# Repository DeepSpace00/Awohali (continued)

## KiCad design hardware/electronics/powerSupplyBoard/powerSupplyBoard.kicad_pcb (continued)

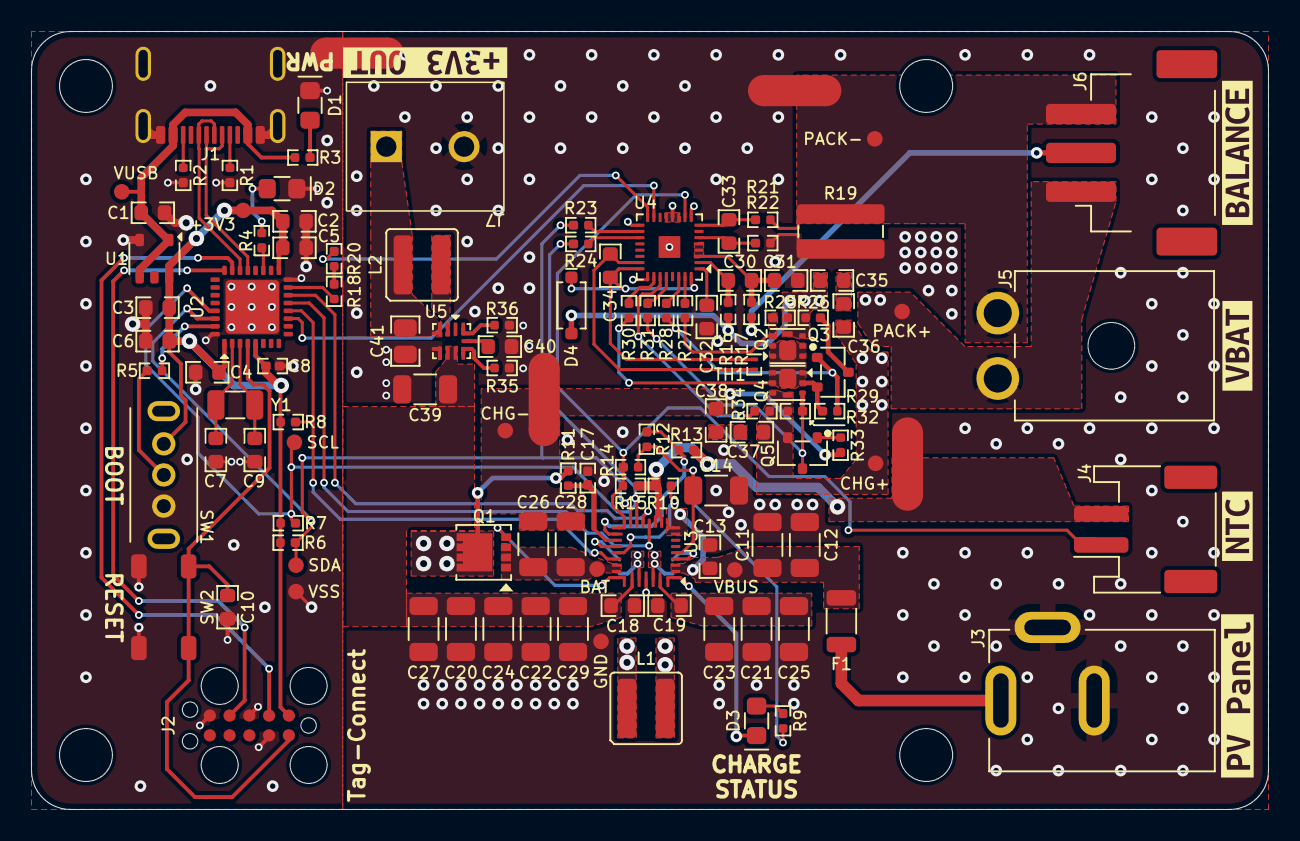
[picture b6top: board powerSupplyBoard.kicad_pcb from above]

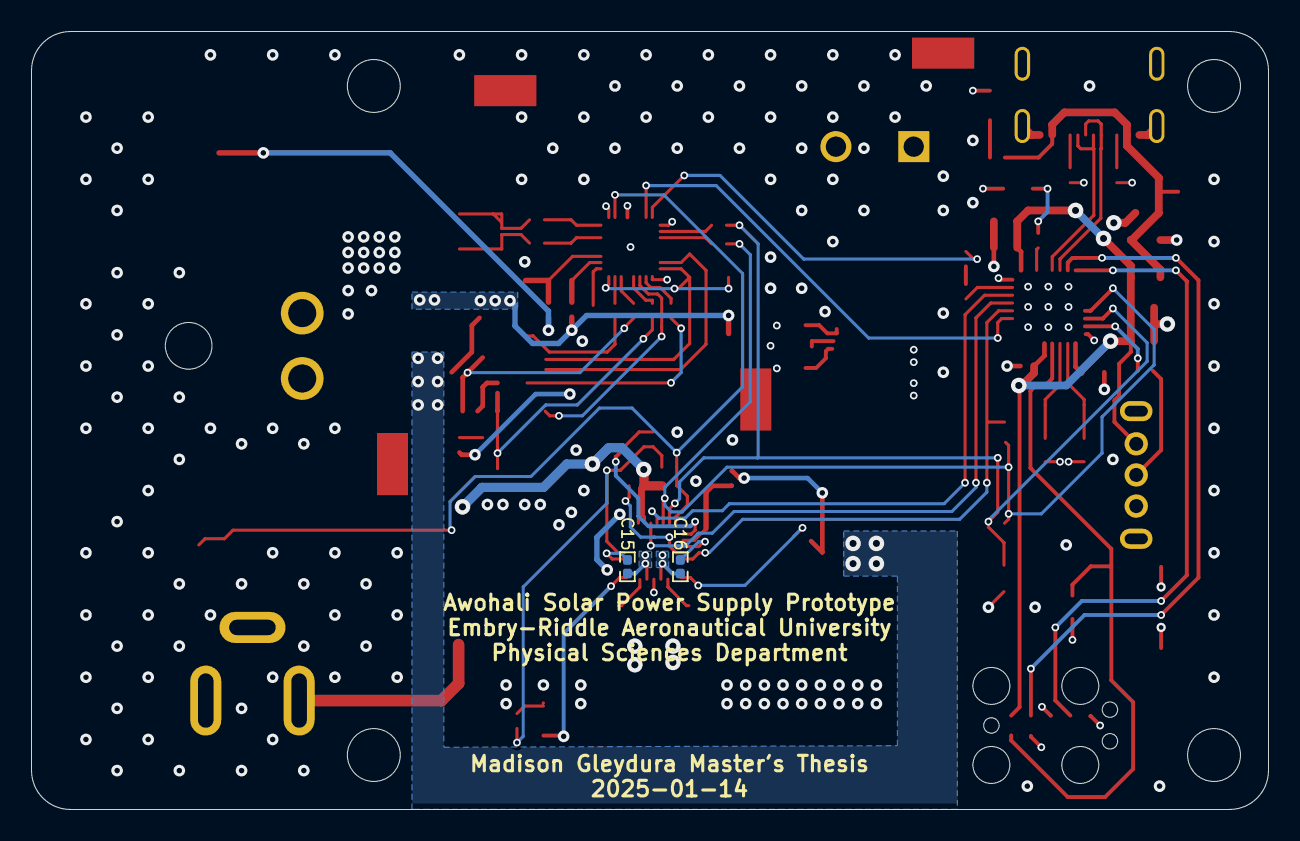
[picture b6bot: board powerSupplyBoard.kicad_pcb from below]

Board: 4 copper layers, 79.5 x 50.0 mm, 130 parts (2 on the bottom side), 77 nets.

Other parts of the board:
kibuzzard-6761C4DA: G***; kibuzzard-6761C4DA
kibuzzard-6761C60F: G***; kibuzzard-6761C60F
kibuzzard-6761CDCC: G***; kibuzzard-6761CDCC
kibuzzard-67280EE7: G***; kibuzzard-67280EE7
kibuzzard-67280F1F: G***; kibuzzard-67280F1F

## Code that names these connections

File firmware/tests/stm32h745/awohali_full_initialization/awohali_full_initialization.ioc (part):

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Mcu.Name=STM32H745ZITx
Mcu.Package=LQFP144
Mcu.UserName=STM32H745ZITx
PA0.GPIOParameters=PinAttribute
PA0.Mode=SD_4_bits_Wide_bus
PA0.PinAttribute=CortexM7
PA0.Signal=SDMMC2_CMD
PA1.GPIOParameters=PinAttribute
PA1.Mode=RMII
PA1.PinAttribute=CortexM7
PA1.Signal=ETH_REF_CLK
PA11.GPIOParameters=PinAttribute
PA11.Mode=Device_Only
PA11.PinAttribute=CortexM7
PA11.Signal=USB_OTG_FS_DM
PA12.GPIOParameters=PinAttribute
PA12.Mode=Device_Only
PA12.PinAttribute=CortexM7
PA12.Signal=USB_OTG_FS_DP
PA13\ (JTMS/SWDIO).GPIOParameters=PinAttribute
PA13\ (JTMS/SWDIO).Mode=Serial_Wire
PA13\ (JTMS/SWDIO).PinAttribute=CortexM7
PA13\ (JTMS/SWDIO).Signal=DEBUG_JTMS-SWDIO
PA14\ (JTCK/SWCLK).GPIOParameters=PinAttribute
PA14\ (JTCK/SWCLK).Mode=Serial_Wire
PA14\ (JTCK/SWCLK).PinAttribute=CortexM7
PA14\ (JTCK/SWCLK).Signal=DEBUG_JTCK-SWCLK
PA2.GPIOParameters=PinAttribute
PA2.Mode=RMII
PA2.PinAttribute=CortexM7
PA2.Signal=ETH_MDIO
PA3.ContextOwner=CortexM4
PA3.GPIOParameters=PinState,GPIO_PuPd,GPIO_Label,PinAttribute
PA3.GPIO_Label=RESET_ETH
PA3.GPIO_PuPd=GPIO_PULLUP
PA3.PinAttribute=CortexM4
PA3.PinState=GPIO_PIN_SET
PA3.Signal=GPIO_Output
PA4.GPIOParameters=PinAttribute
PA4.Mode=NSS_Signal_Hard_Output
PA4.PinAttribute=CortexM4
PA4.Signal=SPI1_NSS
PA5.GPIOParameters=PinAttribute
PA5.Mode=Full_Duplex_Master
PA5.PinAttribute=CortexM4
PA5.Signal=SPI1_SCK
PA6.GPIOParameters=PinAttribute
PA6.Mode=Full_Duplex_Master
PA6.PinAttribute=CortexM4
PA6.Signal=SPI1_MISO
PA7.GPIOParameters=PinAttribute
PA7.Mode=RMII
PA7.PinAttribute=CortexM7
PA7.Signal=ETH_CRS_DV
PA8.GPIOParameters=PinAttribute
PA8.Mode=I2C
PA8.PinAttribute=CortexM4
PA8.Signal=I2C3_SCL
PB0.ContextOwner=CortexM4
PB0.GPIOParameters=GPIO_Label,PinAttribute
PB0.GPIO_Label=HUB_SUSPEND
PB0.PinAttribute=CortexM4
PB0.Signal=GPIO_Output
PB1.ContextOwner=CortexM4
PB1.GPIOParameters=PinState,GPIO_PuPd,GPIO_Label,PinAttribute
PB1.GPIO_Label=RESET_HUB
PB1.GPIO_PuPd=GPIO_PULLUP
PB1.PinAttribute=CortexM4
PB1.PinState=GPIO_PIN_SET
PB1.Signal=GPIO_Output
PB10.GPIOParameters=PinAttribute
PB10.Mode=I2C
PB10.PinAttribute=CortexM4
PB10.Signal=I2C2_SCL
PB11.GPIOParameters=PinAttribute
PB11.Mode=I2C
PB11.PinAttribute=CortexM4
PB11.Signal=I2C2_SDA
PB12.GPIOParameters=PinAttribute
PB12.Mode=RMII
PB12.PinAttribute=CortexM7
PB12.Signal=ETH_TXD0
PB13.GPIOParameters=PinAttribute
PB13.Mode=RMII
PB13.PinAttribute=CortexM7
PB13.Signal=ETH_TXD1
PB14.GPIOParameters=PinAttribute
PB14.Mode=SD_4_bits_Wide_bus
PB14.PinAttribute=CortexM7
PB14.Signal=SDMMC2_D0
PB15.GPIOParameters=PinAttribute
PB15.Mode=SD_4_bits_Wide_bus
PB15.PinAttribute=CortexM7
PB15.Signal=SDMMC2_D1
PB2.ContextOwner=CortexM7
PB2.GPIOParameters=GPIO_Label,PinAttribute
PB2.GPIO_Label=HUB_H7_INT
PB2.PinAttribute=CortexM7
PB2.Signal=GPXTI2
PB3\ (JTDO/TRACESWO).GPIOParameters=PinAttribute
PB3\ (JTDO/TRACESWO).Mode=SD_4_bits_Wide_bus
PB3\ (JTDO/TRACESWO).PinAttribute=CortexM7
PB3\ (JTDO/TRACESWO).Signal=SDMMC2_D2
PB4\ (NJTRST).GPIOParameters=PinAttribute
PB4\ (NJTRST).Mode=SD_4_bits_Wide_bus
PB4\ (NJTRST).PinAttribute=CortexM7
PB4\ (NJTRST).Signal=SDMMC2_D3
PB6.GPIOParameters=PinAttribute
PB6.Mode=I2C
PB6.PinAttribute=CortexM4
PB6.Signal=I2C1_SCL
PB7.GPIOParameters=PinAttribute
PB7.Mode=I2C
PB7.PinAttribute=CortexM4
PB7.Signal=I2C1_SDA
PB9.ContextOwner=CortexM4
PB9.GPIOParameters=GPIO_Label,PinAttribute
PB9.GPIO_Label=NEOPIXEL
PB9.PinAttribute=CortexM4
PB9.Signal=GPIO_Output
PC1.GPIOParameters=PinAttribute
PC1.Mode=RMII
PC1.PinAttribute=CortexM7
PC1.Signal=ETH_MDC
PC10.GPIOParameters=PinAttribute
PC10.Mode=Asynchronous
PC10.PinAttribute=CortexM7
PC10.Signal=UART4_TX
PC11.GPIOParameters=PinAttribute
PC11.Mode=Asynchronous
PC11.PinAttribute=CortexM7
PC11.Signal=UART4_RX
PC13.ContextOwner=CortexM4
PC13.GPIOParameters=GPIO_PuPd,GPIO_Label,PinAttribute
PC13.GPIO_Label=LTE_PWR_EN
PC13.GPIO_PuPd=GPIO_NOPULL
PC13.PinAttribute=CortexM4
PC13.Signal=GPIO_Output
PC14-OSC32_IN\ (OSC32_IN).GPIOParameters=PinAttribute
PC14-OSC32_IN\ (OSC32_IN).Mode=LSE-External-Clock-Source
PC14-OSC32_IN\ (OSC32_IN).PinAttribute=Free
PC14-OSC32_IN\ (OSC32_IN).Signal=RCC_OSC32_IN
PC15-OSC32_OUT\ (OSC32_OUT).ContextOwner=CortexM4
PC15-OSC32_OUT\ (OSC32_OUT).GPIOParameters=PinAttribute
PC15-OSC32_OUT\ (OSC32_OUT).PinAttribute=CortexM4
PC15-OSC32_OUT\ (OSC32_OUT).Signal=GPIO_Output
PC2_C.ContextOwner=CortexM4
PC2_C.GPIOParameters=GPIO_Label,PinAttribute
PC2_C.GPIO_Label=SPI_GRANT
PC2_C.PinAttribute=CortexM4
PC2_C.Signal=GPIO_Output
PC3_C.ContextOwner=CortexM4
PC3_C.GPIOParameters=GPIO_Label,PinAttribute
PC3_C.GPIO_Label=SPI_REQ
PC3_C.PinAttribute=CortexM4
PC3_C.Signal=GPIO_Output
PC4.GPIOParameters=PinAttribute
PC4.Mode=RMII
PC4.PinAttribute=CortexM7
PC4.Signal=ETH_RXD0
PC5.GPIOParameters=PinAttribute
PC5.Mode=RMII
PC5.PinAttribute=CortexM7
PC5.Signal=ETH_RXD1
PC9.GPIOParameters=PinAttribute
PC9.Mode=I2C
PC9.PinAttribute=CortexM4
PC9.Signal=I2C3_SDA
PD0.GPIOParameters=PinAttribute
PD0.Mode=FDCAN_Activate
PD0.PinAttribute=CortexM4
PD0.Signal=FDCAN1_RX
PD1.GPIOParameters=PinAttribute
PD1.Mode=FDCAN_Activate
PD1.PinAttribute=CortexM4
PD1.Signal=FDCAN1_TX
PD2.ContextOwner=CortexM4
PD2.GPIOParameters=GPIO_Label,PinAttribute
PD2.GPIO_Label=H7_CAN_STB
PD2.PinAttribute=CortexM4
PD2.Signal=GPIO_Output
PD3.ContextOwner=CortexM4
PD3.GPIOParameters=GPIO_Label,PinAttribute
PD3.GPIO_Label=RESET_L4_H7
PD3.PinAttribute=CortexM4
PD3.Signal=GPIO_Output
PD4.ContextOwner=CortexM4
PD4.GPIOParameters=GPIO_Label,PinAttribute
PD4.GPIO_Label=BOOT0_L4
PD4.PinAttribute=CortexM4
PD4.Signal=GPIO_Output
PD5.ContextOwner=CortexM4
PD5.GPIOParameters=GPIO_Label,PinAttribute
PD5.GPIO_Label=SPI_SS_L4
PD5.PinAttribute=CortexM4
PD5.Signal=GPXTI5
PD6.GPIOParameters=PinAttribute
PD6.Mode=SD_4_bits_Wide_bus
PD6.PinAttribute=CortexM7
PD6.Signal=SDMMC2_CK
PD7.GPIOParameters=PinAttribute
PD7.Mode=Full_Duplex_Master
PD7.PinAttribute=CortexM4
PD7.Signal=SPI1_MOSI
PD8.GPIOParameters=PinAttribute
PD8.Mode=Asynchronous
PD8.PinAttribute=CortexM4
PD8.Signal=USART3_TX
PD9.GPIOParameters=PinAttribute
PD9.Mode=Asynchronous
PD9.PinAttribute=CortexM4
PD9.Signal=USART3_RX
PE10.ContextOwner=CortexM4
PE10.GPIOParameters=GPIO_Label,PinAttribute
PE10.GPIO_Label=GNSS_PWR_EN
PE10.PinAttribute=CortexM4
PE10.Signal=GPIO_Output
PE11.ContextOwner=CortexM7
PE11.GPIOParameters=GPIO_Label,PinAttribute
PE11.GPIO_Label=GNSS_TX_RDY
PE11.PinAttribute=CortexM7
PE11.Signal=GPIO_Input
PE12.ContextOwner=CortexM7
PE12.GPIOParameters=GPIO_Label,PinAttribute
PE12.GPIO_Label=GNSS_INT
PE12.PinAttribute=CortexM7
PE12.Signal=GPXTI12
PE13.ContextOwner=CortexM7
PE13.GPIOParameters=GPIO_Label,PinAttribute
PE13.GPIO_Label=GNSS_PPS
PE13.PinAttribute=CortexM7
PE13.Signal=GPIO_Input
PE14.ContextOwner=CortexM4
PE14.GPIOParameters=PinState,GPIO_PuPd,GPIO_Label,PinAttribute
PE14.GPIO_Label=RESET_GNSS
PE14.GPIO_PuPd=GPIO_PULLUP
PE14.PinAttribute=CortexM4
PE14.PinState=GPIO_PIN_SET
PE14.Signal=GPIO_Output
PE2.GPIOParameters=PinAttribute
PE2.Mode=Single Bank 1
PE2.PinAttribute=CortexM7
PE2.Signal=QUADSPI_BK1_IO2
PE3.ContextOwner=CortexM4
PE3.GPIOParameters=PinState,GPIO_Label,PinAttribute
PE3.GPIO_Label=RESET_LTE
PE3.PinAttribute=CortexM4
PE3.PinState=GPIO_PIN_SET
PE3.Signal=GPIO_Output
PE4.ContextOwner=CortexM7
PE4.GPIOParameters=GPIO_Label,PinAttribute
PE4.GPIO_Label=MOD_STS
PE4.PinAttribute=CortexM7
PE4.Signal=GPIO_Input
PE5.ContextOwner=CortexM7
PE5.GPIOParameters=GPIO_Label,PinAttribute
PE5.GPIO_Label=NET_STS
PE5.PinAttribute=CortexM7
PE5.Signal=GPIO_Input
PE6.ContextOwner=CortexM4
PE6.GPIOParameters=GPIO_Label,PinAttribute
PE6.GPIO_Label=LTE_SLEEP
PE6.PinAttribute=CortexM4
PE6.Signal=GPIO_Output
PF10.GPIOParameters=PinAttribute
PF10.Mode=Single Bank 1
PF10.PinAttribute=CortexM7
PF10.Signal=QUADSPI_CLK
PF6.GPIOParameters=PinAttribute
PF6.Mode=Single Bank 1
PF6.PinAttribute=CortexM7
PF6.Signal=QUADSPI_BK1_IO3
PF8.GPIOParameters=PinAttribute
PF8.Mode=Single Bank 1
PF8.PinAttribute=CortexM7
PF8.Signal=QUADSPI_BK1_IO0
PF9.GPIOParameters=PinAttribute
PF9.Mode=Single Bank 1
PF9.PinAttribute=CortexM7
PF9.Signal=QUADSPI_BK1_IO1
PG11.GPIOParameters=PinAttribute
PG11.Mode=RMII
PG11.PinAttribute=CortexM7
PG11.Signal=ETH_TX_EN
PG6.GPIOParameters=PinAttribute
PG6.Mode=Single Bank 1
PG6.PinAttribute=CortexM7
PG6.Signal=QUADSPI_BK1_NCS
PH0-OSC_IN\ (PH0).GPIOParameters=PinAttribute
PH0-OSC_IN\ (PH0).Mode=HSE-External-Clock-Source
PH0-OSC_IN\ (PH0).PinAttribute=Free
PH0-OSC_IN\ (PH0).Signal=RCC_OSC_IN
RCC.SYSCLKFreq_VALUE=64000000
board=custom

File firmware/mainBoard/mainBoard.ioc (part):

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Mcu.Name=STM32H745ZITx
Mcu.Package=LQFP144
Mcu.UserName=STM32H745ZITx
PA0.GPIOParameters=PinAttribute
PA0.Mode=SD_4_bits_Wide_bus
PA0.PinAttribute=CortexM7
PA0.Signal=SDMMC2_CMD
PA1.GPIOParameters=PinAttribute
PA1.Mode=RMII
PA1.PinAttribute=CortexM7
PA1.Signal=ETH_REF_CLK
PA11.GPIOParameters=PinAttribute
PA11.Mode=Device_Only
PA11.PinAttribute=CortexM7
PA11.Signal=USB_OTG_FS_DM
PA12.GPIOParameters=PinAttribute
PA12.Mode=Device_Only
PA12.PinAttribute=CortexM7
PA12.Signal=USB_OTG_FS_DP
PA13\ (JTMS/SWDIO).GPIOParameters=PinAttribute
PA13\ (JTMS/SWDIO).Mode=Serial_Wire
PA13\ (JTMS/SWDIO).PinAttribute=CortexM7
PA13\ (JTMS/SWDIO).Signal=DEBUG_JTMS-SWDIO
PA14\ (JTCK/SWCLK).GPIOParameters=PinAttribute
PA14\ (JTCK/SWCLK).Mode=Serial_Wire
PA14\ (JTCK/SWCLK).PinAttribute=CortexM7
PA14\ (JTCK/SWCLK).Signal=DEBUG_JTCK-SWCLK
PA2.GPIOParameters=PinAttribute
PA2.Mode=RMII
PA2.PinAttribute=CortexM7
PA2.Signal=ETH_MDIO
PA7.GPIOParameters=PinAttribute
PA7.Mode=RMII
PA7.PinAttribute=CortexM7
PA7.Signal=ETH_CRS_DV
PA8.GPIOParameters=PinAttribute
PA8.Mode=I2C
PA8.PinAttribute=CortexM7
PA8.Signal=I2C3_SCL
PB10.GPIOParameters=PinAttribute
PB10.Mode=I2C
PB10.PinAttribute=CortexM7
PB10.Signal=I2C2_SCL
PB11.GPIOParameters=PinAttribute
PB11.Mode=I2C
PB11.PinAttribute=CortexM7
PB11.Signal=I2C2_SDA
PB12.GPIOParameters=PinAttribute
PB12.Mode=RMII
PB12.PinAttribute=CortexM7
PB12.Signal=ETH_TXD0
PB13.GPIOParameters=PinAttribute
PB13.Mode=RMII
PB13.PinAttribute=CortexM7
PB13.Signal=ETH_TXD1
PB14.GPIOParameters=PinAttribute
PB14.Mode=SD_4_bits_Wide_bus
PB14.PinAttribute=CortexM7
PB14.Signal=SDMMC2_D0
PB15.GPIOParameters=PinAttribute
PB15.Mode=SD_4_bits_Wide_bus
PB15.PinAttribute=CortexM7
PB15.Signal=SDMMC2_D1
PB3\ (JTDO/TRACESWO).GPIOParameters=PinAttribute
PB3\ (JTDO/TRACESWO).Mode=SD_4_bits_Wide_bus
PB3\ (JTDO/TRACESWO).PinAttribute=CortexM7
PB3\ (JTDO/TRACESWO).Signal=SDMMC2_D2
PB4\ (NJTRST).GPIOParameters=PinAttribute
PB4\ (NJTRST).Mode=SD_4_bits_Wide_bus
PB4\ (NJTRST).PinAttribute=CortexM7
PB4\ (NJTRST).Signal=SDMMC2_D3
PB6.GPIOParameters=PinAttribute
PB6.Mode=I2C
PB6.PinAttribute=CortexM7
PB6.Signal=I2C1_SCL
PB7.GPIOParameters=PinAttribute
PB7.Mode=I2C
PB7.PinAttribute=CortexM7
PB7.Signal=I2C1_SDA
PC1.GPIOParameters=PinAttribute
PC1.Mode=RMII
PC1.PinAttribute=CortexM7
PC1.Signal=ETH_MDC
PC10.GPIOParameters=PinAttribute
PC10.Mode=Asynchronous
PC10.PinAttribute=CortexM7
PC10.Signal=UART4_TX
PC11.GPIOParameters=PinAttribute
PC11.Mode=Asynchronous
PC11.PinAttribute=CortexM7
PC11.Signal=UART4_RX
PC12.GPIOParameters=PinAttribute
PC12.Mode=Asynchronous
PC12.PinAttribute=CortexM7
PC12.Signal=UART5_TX
PC14-OSC32_IN\ (OSC32_IN).GPIOParameters=PinAttribute
PC14-OSC32_IN\ (OSC32_IN).Mode=LSE-External-Clock-Source
PC14-OSC32_IN\ (OSC32_IN).PinAttribute=Free
PC14-OSC32_IN\ (OSC32_IN).Signal=RCC_OSC32_IN
PC4.GPIOParameters=PinAttribute
PC4.Mode=RMII
PC4.PinAttribute=CortexM7
PC4.Signal=ETH_RXD0
PC5.GPIOParameters=PinAttribute
PC5.Mode=RMII
PC5.PinAttribute=CortexM7
PC5.Signal=ETH_RXD1
PC7.GPIOParameters=PinAttribute
PC7.Mode=Asynchronous
PC7.PinAttribute=CortexM7
PC7.Signal=USART6_RX
PC9.GPIOParameters=PinAttribute
PC9.Mode=I2C
PC9.PinAttribute=CortexM7
PC9.Signal=I2C3_SDA
PD0.GPIOParameters=PinAttribute
PD0.Mode=FDCAN_Activate
PD0.PinAttribute=CortexM7
PD0.Signal=FDCAN1_RX
PD1.GPIOParameters=PinAttribute
PD1.Mode=FDCAN_Activate
PD1.PinAttribute=CortexM7
PD1.Signal=FDCAN1_TX
PD11.GPIOParameters=PinAttribute
PD11.Mode=CTS_RTS
PD11.PinAttribute=CortexM7
PD11.Signal=USART3_CTS
PD12.GPIOParameters=PinAttribute
PD12.Mode=CTS_RTS
PD12.PinAttribute=CortexM7
PD12.Signal=USART3_RTS
PD2.GPIOParameters=PinAttribute
PD2.Mode=Asynchronous
PD2.PinAttribute=CortexM7
PD2.Signal=UART5_RX
PD6.GPIOParameters=PinAttribute
PD6.Mode=SD_4_bits_Wide_bus
PD6.PinAttribute=CortexM7
PD6.Signal=SDMMC2_CK
PD8.GPIOParameters=PinAttribute
PD8.Mode=Asynchronous
PD8.PinAttribute=CortexM7
PD8.Signal=USART3_TX
PD9.GPIOParameters=PinAttribute
PD9.Mode=Asynchronous
PD9.PinAttribute=CortexM7
PD9.Signal=USART3_RX
PE2.GPIOParameters=PinAttribute
PE2.Mode=Single Bank 1
PE2.PinAttribute=CortexM7
PE2.Signal=QUADSPI_BK1_IO2
PE7.GPIOParameters=PinAttribute
PE7.Mode=Asynchronous
PE7.PinAttribute=CortexM7
PE7.Signal=UART7_RX
PF10.GPIOParameters=PinAttribute
PF10.Mode=Single Bank 1
PF10.PinAttribute=CortexM7
PF10.Signal=QUADSPI_CLK
PF14.GPIOParameters=PinAttribute
PF14.Mode=I2C
PF14.PinAttribute=CortexM7
PF14.Signal=I2C4_SCL
PF15.GPIOParameters=PinAttribute
PF15.Mode=I2C
PF15.PinAttribute=CortexM7
PF15.Signal=I2C4_SDA
PF6.GPIOParameters=PinAttribute
PF6.Mode=Single Bank 1
PF6.PinAttribute=CortexM7
PF6.Signal=QUADSPI_BK1_IO3
PF7.GPIOParameters=PinAttribute
PF7.Mode=Asynchronous
PF7.PinAttribute=CortexM7
PF7.Signal=UART7_TX
PF8.GPIOParameters=PinAttribute
PF8.Mode=Single Bank 1
PF8.PinAttribute=CortexM7
PF8.Signal=QUADSPI_BK1_IO0
PF9.GPIOParameters=PinAttribute
PF9.Mode=Single Bank 1
PF9.PinAttribute=CortexM7
PF9.Signal=QUADSPI_BK1_IO1
PG11.GPIOParameters=PinAttribute
PG11.Mode=RMII
PG11.PinAttribute=CortexM7
PG11.Signal=ETH_TX_EN
PG13.GPIOParameters=PinAttribute
PG13.Mode=CTS_RTS
PG13.PinAttribute=CortexM7
PG13.Signal=USART6_CTS
PG14.GPIOParameters=PinAttribute
PG14.Mode=Asynchronous
PG14.PinAttribute=CortexM7
PG14.Signal=USART6_TX
PG6.GPIOParameters=PinAttribute
PG6.Mode=Single Bank 1
PG6.PinAttribute=CortexM7
PG6.Signal=QUADSPI_BK1_NCS
PG8.GPIOParameters=PinAttribute
PG8.Mode=CTS_RTS
PG8.PinAttribute=CortexM7
PG8.Signal=USART6_RTS
PH0-OSC_IN\ (PH0).GPIOParameters=PinAttribute
PH0-OSC_IN\ (PH0).Mode=HSE-External-Clock-Source
PH0-OSC_IN\ (PH0).PinAttribute=Free
PH0-OSC_IN\ (PH0).Signal=RCC_OSC_IN
RCC.SYSCLKFreq_VALUE=64000000
board=custom

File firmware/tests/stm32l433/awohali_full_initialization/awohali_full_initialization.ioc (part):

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Mcu.Name=STM32L433C(B-C)Ux
Mcu.Package=UFQFPN48
Mcu.UserName=STM32L433CCUx
PA0.GPIOParameters=GPIO_Label
PA0.GPIO_Label=CAN_STB
PA0.Signal=GPIO_Output
PA1.Mode=Full_Duplex_Master
PA1.Signal=SPI1_SCK
PA10.Mode=I2C
PA10.Signal=I2C1_SDA
PA11.Mode=Device
PA11.Signal=USB_DM
PA12.Mode=Device
PA12.Signal=USB_DP
PA13\ (JTMS-SWDIO).Mode=Serial_Wire
PA13\ (JTMS-SWDIO).Signal=SYS_JTMS-SWDIO
PA14\ (JTCK-SWCLK).Mode=Serial_Wire
PA14\ (JTCK-SWCLK).Signal=SYS_JTCK-SWCLK
PA15\ (JTDI).GPIOParameters=GPIO_Label
PA15\ (JTDI).GPIO_Label=PG_2V8
PA15\ (JTDI).Signal=GPIO_Input
PA2.GPIOParameters=GPIO_Label
PA2.GPIO_Label=BAT_CHG_INT
PA2.Signal=GPXTI2
PA3.GPIOParameters=PinState,GPIO_Label
PA3.GPIO_Label=EEPROM_WC
PA3.PinState=GPIO_PIN_SET
PA3.Signal=GPIO_Output
PA4.Mode=NSS_Signal_Hard_Output
PA4.Signal=SPI1_NSS
PA5.GPIOParameters=GPIO_Label
PA5.GPIO_Label=BOOT_H7
PA5.Signal=GPIO_Output
PA6.Mode=Full_Duplex_Master
PA6.Signal=SPI1_MISO
PA7.Mode=Full_Duplex_Master
PA7.Signal=SPI1_MOSI
PA8.GPIOParameters=GPIO_Label
PA8.GPIO_Label=SS_L4
PA8.Signal=GPIO_Input
PA9.Mode=I2C
PA9.Signal=I2C1_SCL
PB1.GPIOParameters=GPIO_Label
PB1.GPIO_Label=PG_1V8
PB1.Signal=GPIO_Input
PB10.GPIOParameters=GPIO_Label
PB10.GPIO_Label=PG_3V3
PB10.Signal=GPIO_Input
PB11.GPIOParameters=GPIO_Label
PB11.GPIO_Label=BAL_ALERT
PB11.Signal=GPIO_Input
PB12.GPIOParameters=GPIO_Label
PB12.GPIO_Label=SPI1_GRANT
PB12.Signal=GPIO_Output
PB13.GPIOParameters=GPIO_Label
PB13.GPIO_Label=SPI1_REQ
PB13.Signal=GPIO_Output
PB14.GPIOParameters=PinState,GPIO_Label
PB14.GPIO_Label=QON
PB14.PinState=GPIO_PIN_SET
PB14.Signal=GPIO_Output
PB15.GPIOParameters=PinState,GPIO_Label
PB15.GPIO_Label=CE
PB15.PinState=GPIO_PIN_SET
PB15.Signal=GPIO_Output
PB2.GPIOParameters=GPIO_Label
PB2.GPIO_Label=EN_1V8
PB2.Signal=GPIO_Output
PB3\ (JTDO-TRACESWO).GPIOParameters=GPIO_Label
PB3\ (JTDO-TRACESWO).GPIO_Label=EN_2V8
PB3\ (JTDO-TRACESWO).Signal=GPIO_Output
PB4\ (NJTRST).GPIOParameters=GPIO_Label
PB4\ (NJTRST).GPIO_Label=RESET_H7
PB4\ (NJTRST).Signal=GPIO_Output
PB6.GPIOParameters=GPIO_Label
PB6.GPIO_Label=HUB_INT
PB6.Signal=GPXTI6
PB8.Mode=CAN_Activate
PB8.Signal=CAN1_RX
PB9.Mode=CAN_Activate
PB9.Signal=CAN1_TX
PC14-OSC32_IN\ (PC14).Mode=LSE-External-Clock-Source
PC14-OSC32_IN\ (PC14).Signal=RCC_OSC32_IN
PH0-OSC_IN\ (PH0).GPIOParameters=GPIO_Label
PH0-OSC_IN\ (PH0).GPIO_Label=NEOPIXEL_DIN
PH0-OSC_IN\ (PH0).Signal=GPIO_Output
PH1-OSC_OUT\ (PH1).GPIOParameters=GPIO_Label
PH1-OSC_OUT\ (PH1).GPIO_Label=LED_BUILTIN
PH1-OSC_OUT\ (PH1).Signal=GPIO_Output
RCC.HSE_VALUE=8000000
RCC.SYSCLKFreq_VALUE=80000000
RCC.SYSCLKSource=RCC_SYSCLKSOURCE_PLLCLK
board=custom

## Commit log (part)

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2025-08-18 removed unneeded wire instance
2025-08-18 removed unneeded serial instance
2025-08-18 dont need to init serial here
2025-08-18 dont need to set init flag here
2025-08-18 redundant
2025-08-18 init i2c stuff
2025-08-18 don't need deinit function
2025-08-18 init uart stuff
2025-08-18 set status type
2025-08-18 made address const
2025-08-18 removed unneeded vars
2025-08-18 gnss driver stuff
2025-08-19 rewrote GNSS driver
2025-08-22 added functions to get ubx-mon-ver info
2025-08-22 redid example to just get version info
    Just a test to make sure we can establish communication with the module
2025-08-25 created examples for gnss
2025-08-27 renamed folders
2025-09-10 added tests for setting up GNSS LNA for testing
2025-09-10 set up GNSS LNA testing
2025-09-10 updated driver to better handle UBX commands. added layer param to config functions.
2025-09-10 fixed typedefs and rearanged stuff
2025-09-11 fixed driver
2025-09-11 added words to dict
2025-09-11 added pyubx2 package req
2025-09-11 moved file
2025-09-11 testing parsing UBX data file
2025-09-11 switched data message type
2025-09-14 fixed driver i think. added script to record data
2025-09-15 changes ig
2025-09-18 created files
2025-09-18 finally got GPS logging working
2025-09-18 new data files
2025-09-18 fixed timing and disabled galileo and glonass
2025-09-18 new data
2025-09-19 new data!
2025-09-19 fixed parser to properly timestamp data
2025-09-19 debug statements
2025-09-19 path stuff from saving
2025-09-19 moved data
2025-09-19 added pandas to deps
2025-09-19 time stuff
2025-09-19 converted file for UBX 2
2025-09-19 cleaned up code
2025-09-19 new (good) data!
2025-09-19 paths
2025-09-19 added Galileo sats and reverted message rate back to 1Hz
2025-09-23 more data
2025-09-23 measurement rate
2025-09-23 whatever this xml stuff is ig
2025-09-23 setup gnss logging stm32 projects for both cores
2025-09-26 started writing new logging code
2025-09-28 data
2025-09-28 trying to fix RAWX nav rate
2025-09-28 finally, some good data
2025-09-28 we need a .gitignore for this stuff
2025-09-28 command for parsing ubx file
2025-09-28 git ignore for CLion XML files. finally...
2025-09-28 removed old XML files
2025-09-29 python stuff
2025-09-29 created new ubx parser for more message types
2025-09-29 fixed for logging more messages
2025-09-29 fixed nav rate
2025-09-29 removed pyubx2 package. manually parsing ubx files now
2025-09-29 added root build dir
2025-09-29 editor changes
2025-09-29 fix addresses
2025-09-29 processing data
2025-09-29 copied latest driver to src folder
2025-09-29 deleted blank line
2025-10-01 adding USB hub initialization to program
2025-10-01 removed uneeded build, cache, and editor files
2025-10-02 evk data
2025-10-02 data!
2025-10-03 unneeded scripts
2025-10-03 old files
2025-10-03 new JSONs
2025-10-03 fixed scripts
2025-10-03 test data
2025-10-03 renamed files
2025-10-03 processed new data
2025-10-05 fixing code to log on mainboard
2025-10-07 data logged with pygpsclient
2025-10-08 files deleted
2025-10-08 added CLion ignores
2025-10-08 c_cpp_properties for workspace
2025-10-08 not sure. going to stop tracking anyways
2025-10-08 test to init usb hub with STM32H745
2025-10-08 moved to new temp dir until other system stuff is fixed
2025-10-08 removed untracked files
2025-10-08 removed files
2025-10-08 re-added submodule
2025-10-13 removed some files from .gitignore
2025-10-13 readded files
2025-10-13 removed .iml ignore
2025-10-13 iml's
2025-10-13 clean blink example for CubeIDE
2025-10-13 broken
2025-10-13 playing with settings
2025-10-13 trying to get it working
2025-10-13 clean CLion CMake example. use this as a template for new projects. does work (on office PC, need to test for home)
2025-10-13 renamed folder
2025-10-13 generated files
2025-10-13 configured for build
2025-10-15 removed
2025-10-15 modified for USB hub init only
2025-10-15 added USB hub files
2025-10-15 removed FatFs files
2025-10-15 fixed blink code location
2025-10-15 added USB stuff to main.h
2025-10-15 removed unneeded HALs
2025-10-15 added usb init code
2025-10-15 removed old GPIO clock stuff
2025-10-15 added usb hub stuff
2025-11-10 radar beam blockage - KGSP
2025-11-13 exported cad
2025-11-13 workspace stuff
2025-11-13 fixing ephemeric and georange code
2025-11-13 remove image
2025-11-14 created new sfrbx parser to make sure it is 100% correct.
2025-11-14 replaced with new file
2025-11-14 new ephemeris data
2025-11-14 table structure for message types
2025-11-14 pycharm stuff
2025-11-14 moved to subfolder
2025-11-14 moved to data folder
2025-11-14 moved to "old" subfolder
2025-11-17 trying to get Galileo code working
2025-11-17 working Galileo ephemeris parser
2025-11-18 working ephemeris for Galileo
2025-11-18 fixing geometric range code
2025-11-18 exported model for LPS28 mount
2025-11-21 removed old files
2025-11-21 RINEX data from Ormond BEach municipal airport CORS receiver
2025-11-21 parsed ephemeris data from CORS
2025-11-21 old versions
2025-11-21 renamed file
2025-11-21 fixed code with correct time corrections
2025-11-21 examples for how to call functions from geometric_range
2025-11-21 some pycharm file. might need to add to gitignore
2025-11-21 fixed mount profiles
2025-11-21 UBX data from 2025-10-03
2025-11-24 Working on fixing timing issues
2025-11-24 moved ephemerides to subfolder
2025-11-24 renamed files and moved to old folder
2025-11-24 broke out into separate file
2025-11-24 fixed code
2025-11-24 reformatted name for sqrt_A parameter
2025-11-24 contains all stuff including clock correction
2025-11-24 limited to only calculating geometric range
2025-11-24 calculating pseudorange residuals (primarily tropospheric delay)
2025-11-25 CLion stuff
2025-11-25 fixed printf type formatting and temporarily disabled coordinate logging
2025-11-25 calc for new data
2025-11-25 removed CSVs
2025-11-26 moved files
2025-11-26 without utc timestamp
2025-11-26 modified code
2025-11-26 code to analyze pseudorange
2025-11-26 unsorted data
2025-11-30 fixes to code to process all data
2025-11-30 ormond beach data
2025-11-30 ESA data
2025-11-30 plots
2025-11-30 sample data
2025-11-30 parsed ubx data
2025-11-30 database files
2025-11-30 todo list
2025-11-30 rinex broadcast ephemeris
2025-11-30 fixing code
2025-11-30 new ephemeris
2025-12-01 added clarification for what ephemeris is considered valid
2025-12-01 fixed dict structures
2025-12-01 cleaned up vars, set ref time to gpsTOW, and new data dirs
2025-12-01 fixed some stuff related to gpsTOW and getting ZED-F9P data to look right
2025-12-01 trying to see what is going on with ZED-F9P data
2025-12-01 updated .gitignore
2025-12-01 stop tracking PyCharm workspace file
2025-12-01 Stop traching PyCharm cpython files
2025-12-01 re-ran data
2025-12-01 fixed rcv bias calc
2025-12-01 stop tracking
2025-12-01 added pycache to gitignore
2025-12-03 best data so far
2025-12-03 csv output from db
2025-12-03 added code to fix iTOW/rcvTOW syncing issues
2025-12-08 created
2025-12-09 pwv data
2025-12-09 VMF stuff
2025-12-10 fixed code for ZTD and added ionosphere correction stuff
2025-12-20 simplified code and added more message types in driver
2025-12-20 removed old example
2025-12-20 updated driver
2025-12-20 changed plots
2025-12-27 trying to port datalogger code to Pico-SDK
2025-12-27 stoped tracking files
2025-12-27 ignore .idea/ dir
2025-12-27 Pico SDK version of gnss datalogger
2025-12-27 added UART DMA control
2025-12-27 globally ignore any .idea/ directory
2025-12-27 stop tracking files
2025-12-27 stopped tracking files
2025-12-27 renamed dirs
2025-12-27 moved images
2025-12-27 updated datasheet refs
2025-12-27 re-plotted schematics and layout files
2025-12-27 removed script
2025-12-27 moved everything to Python subfolder
2025-12-27 moved Python folder up a directory
2025-12-27 renamed dir
2025-12-27 moved scripts
2025-12-27 moved script
2025-12-27 created Python .gitignore
2025-12-27 created README.md
2025-12-27 updated copyright date
2025-12-27 re-added hardware license
2026-01-16 config file stuff
2026-01-16 fixed table formatting
2026-01-16 dsad
2026-01-21 ran new data
2026-01-21 trying to fix outputs
2026-01-21 added status bar to output
2026-01-23 trying to get trop delay fixed. not working : (
2026-01-30 scripts to pull precip data over date range in region
2026-01-30 results from regional precip data
2026-02-17 fixed page name spelling
2026-02-26 fixed file names
2026-02-26 added west dir to gitignore
2026-02-27 define all pins for H7 part of board
2026-02-27 fixed pin directions
2026-02-27 removed file
2026-02-27 removed redundant ignore dir
2026-02-27 added new Zephyr instructions
2026-02-27 added new .gitignore
2026-02-27 added
2026-02-27 board defs for H7 microcontroller
2026-02-27 Zephyr test application
2026-03-02 added i2c scanner app
2026-03-02 added README.md
2026-03-02 added i2c scan app
2026-03-02 added lps2xdf sample app
2026-03-02 added sht4x sample app
2026-03-02 renamed app
2026-03-02 full init of all pins
2026-03-02 renames and add devicetree bindings for ICs
2026-03-03 renamed board
2026-03-03 deleted overlay
2026-03-03 devicetree bindings for ICs
2026-03-03 zepher-ide settings for vscode
2026-03-03 zephyr paths
2026-03-03 added gitignore for vscode folder
2026-03-03 configure USB2422 at the begining of each boot
2026-03-03 extensions
2026-03-12 overlays for Awohali
2026-03-12 fixed boolean type defs
2026-03-12 added board varients
2026-03-12 fixed board defs for the L433 uC
2026-03-12 started to fix board defs for the H745 uC
2026-03-12 removed dts check
2026-03-12 debug optimizations
2026-03-12 added more board defs
2026-03-12 changed print
2026-03-12 overlays
2026-03-12 added stuff for L4
2026-03-13 fixed Galileo ephemeris code
2026-03-16 data plots
2026-03-16 calculations
2026-03-16 new DBs
2026-03-16 new eph
2026-03-16 new RINEX data
2026-03-16 new DB
2026-03-16 VMF data
2026-03-16 fixed parsing
2026-03-16 combine pseudorange and calc pwv
2026-03-16 fixed
2026-03-16 compare data for RINEX and UBX
2026-03-16 wmf3_grid converted from matlab
2026-03-17 removed plots
2026-03-17 correct el az plots
2026-03-17 trying to fix UBX data
2026-03-18 zed-f9p
2026-03-18 reigned in ZTD and PWV calculations
2026-03-18 combined pyproject's
2026-03-18 added figures path to .gitignore
2026-03-21 parsed more data
2026-03-21 updated ephemerides
2026-03-21 CDIS RINEX NAV messages
2026-03-21 check if ZTD is good
2026-03-21 fixed parsers
2026-03-21 added Kalman filter
2026-03-21 plot data
2026-03-21 fix code
2026-03-21 added function
2026-03-27 re-tracking drivers
2026-03-27 offload files to NAS
2026-03-27 moved to VMF3 subdir
2026-03-27 LaTeX plotting
2026-04-03 added data folder to .gitignore
2026-04-03 removed old scripts
2026-04-03 trying to fix data
2026-04-10 compare raPPPid data
